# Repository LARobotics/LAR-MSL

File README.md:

# LAR@MSL

## Links
 - [Website] <https://lar.dei.uminho.pt/>
 - [Youtube] <https://www.youtube.com/@lar_uminho>
 - [Instagram] <https://www.instagram.com/lar_uminho>
 - [TikTok] <https://www.tiktok.com/@lar_uminho>
 - [Facebook] <https://www.facebook.com/profile.php?id=100088692420376>

## Our robot: 

# Base Station and Strategy:
The Base Station and Strategy was developed in Python 3.11 and is one of the most important tools for the robots to be able to play. It handles the communications between the Base Station and the robots and even from the RefBox using WebSockets. The Strategy works with the inputs from the robots, calculates the group of skills for that game state, and gives that information back to the robots.

# Calibration Tools:
This folder contains Calibration tools to simplify the calibration of cameras and their alignment. It was made in Python and saves a lot of time when the robot is disassembled and needs to be calibrated.

# Hardware and 3D CADS
Here are available the 3D CAD files from the robot, which is made by either aluminium or plastic PLA. There are still hardware being developed and some of them are from previous team generations, but the ones made this year are available here.

# Player
This is the main robot code that runs on the robot's main computer. It also has the ESP32 code that runs on the Robot Microcontroller.

# Tutorial
Here are some tutorials for the things that are used by the team, for example the use of YOLO, Cameras through Ethernet, Ubuntu installation etc…

# Yolo
In this folder are available Datasets and Code that are used by the Team. It is also being made a version of running the Yolo network in Golang, the language used in the Robot.

### Contacts
 - <fernando@dei.uminho.pt>
 - <gil@dei.uminho.pt>

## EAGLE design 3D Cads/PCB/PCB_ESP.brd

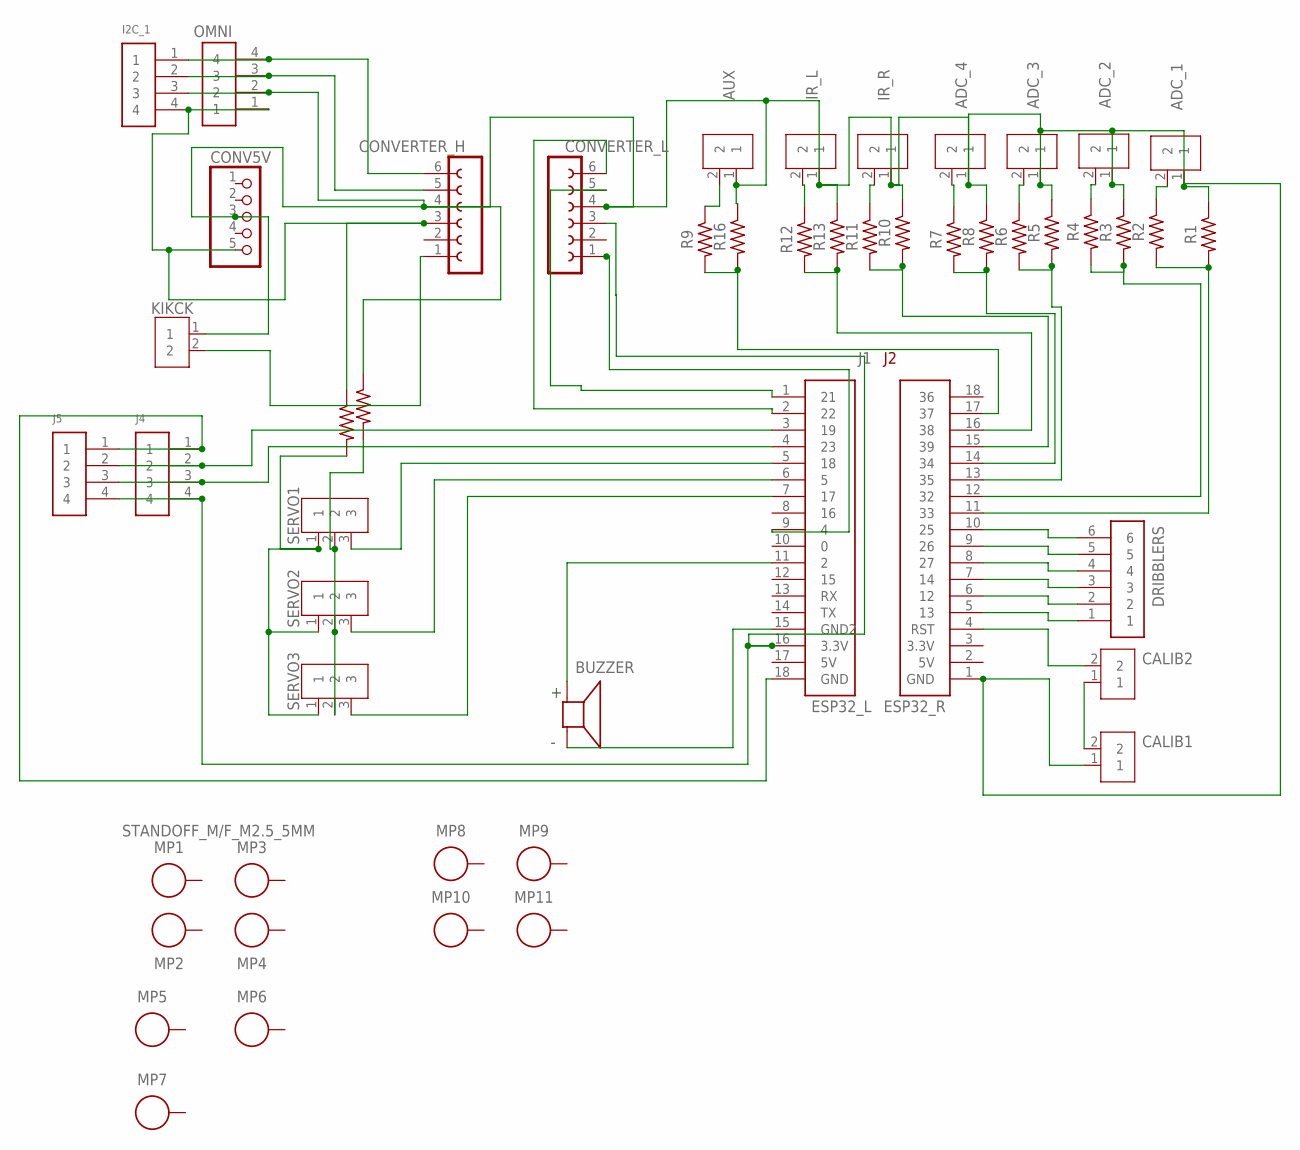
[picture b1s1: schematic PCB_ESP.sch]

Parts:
ADC_1, ADC_2, ADC_3, ADC_4: 2828XX-2282834-2; TERMBLK_254-2N
AUX: 2828XX-2282834-2; TERMBLK_254-2N
BUZZER: AT-1220-TT-9-R; XDCR_AT-1220-TT-9-R
CALIB1, CALIB2: 2828XX-2282834-2; TERMBLK_254-2N
CONV5V: PINHD-1X55X2MM; 1_05X2MM
CONVERTER_H: FE06-1; FE06
CONVERTER_L: FE06-1; FE06
DRIBBLERS: 61300611121
I2C_1: 61300411121
IR_L: 2828XX-2282834-2; TERMBLK_254-2N
IR_R: 2828XX-2282834-2; TERMBLK_254-2N
J1: ESP32_L; 61301811121
J2: ESP32_R; 61301811121
J4, J5: 61300411121
KIKCK: 2828XX-2282834-2; TERMBLK_254-2N
MP1, MP2, MP3, MP4, MP5, MP6, MP7: STANDOFF_M/F_M2.5_5MM; STANDOFF_HEX_MALE-FEMALE_500X500_M2.5X0.45_MTGP755H270
MP8, MP9, MP10, MP11: STANDOFF_F/F_M2.5_5MM; STANDOFF_HEX_FEMALE_500X500_M2.5X0.45_MTGP755H270
OMNI: 61300411121
R1, R2, R3, R4, R5, R6, R7, R8, R9, R10, R11, R12, R13, R14, R15, R16: R-US_AXIAL-7.2MM-PITCH; RESAD724W46L381D178B
SERVO1, SERVO2, SERVO3: 2828XX-3282834-3; TERMBLK_254-3N

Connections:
unnamed: DRIBBLERS.1, J2.5 (13)
unnamed: J2.12 (32), R3.2, R4.2
unnamed: ADC_2.2, R4.1
unnamed: CONVERTER_H.1, KIKCK.2
unnamed: CONVERTER_H.6, I2C_1.1, OMNI.4
unnamed: J2.14 (34), R7.2, R8.2
unnamed: CONVERTER_H.5, I2C_1.2, OMNI.3
unnamed: AUX.2, R9.1
unnamed: J2.13 (35), R5.2, R6.2
unnamed: CONVERTER_L.5, J1.1 (21)
unnamed: CONVERTER_L.6, J1.2 (22)
unnamed: ADC_4.2, R7.1
unnamed: BUZZER.N, J1.15 (GND2)
unnamed: ADC_3.2, R6.1
unnamed: CONV5V.5, CONVERTER_H.3, I2C_1.4, OMNI.1, R14.1
unnamed: BUZZER.P, J1.11 (2)
unnamed: ADC_1.1, ADC_2.1, ADC_3.1, ADC_4.1, AUX.1, CALIB1.1, CONV5V.3, CONVERTER_H.4, CONVERTER_L.4, I2C_1.3, IR_L.1, IR_R.1, J2.1 (GND), KIKCK.1, OMNI.2, R1.1, R3.1, R5.1, R8.1, R10.1, R13.1, R15.1, R16.1
unnamed: CALIB2.2, J2.4 (RST)
unnamed: DRIBBLERS.2, J2.6 (12)
unnamed: DRIBBLERS.3, J2.7 (14)
unnamed: DRIBBLERS.4, J2.8 (27)
unnamed: DRIBBLERS.5, J2.9 (26)
unnamed: DRIBBLERS.6, J2.10 (25)
unnamed: CALIB1.2, CALIB2.1
unnamed: ADC_1.2, R2.1
unnamed: CONVERTER_L.1, J1.9 (4)
unnamed: J2.11 (33), R1.2, R2.2
unnamed: J2.15 (39), R10.2, R11.2
unnamed: IR_L.2, R12.1
unnamed: IR_R.2, R11.1
unnamed: J1.18 (GND), J4.1, J5.1
unnamed: J2.17 (37), R9.2, R16.2
unnamed: J2.16 (38), R12.2, R13.2
unnamed: R14.2, SERVO1.1, SERVO2.1, SERVO3.1
unnamed: R15.2, SERVO1.2, SERVO2.2, SERVO3.2
unnamed: J1.5 (18), SERVO1.3
unnamed: J1.6 (5), SERVO2.3
unnamed: J1.7 (17), SERVO3.3
unnamed: J1.3 (19), J4.2, J5.2
unnamed: J1.4 (23), J4.3, J5.3
unnamed: CONVERTER_L.3, J1.16 (3.3V), J4.4, J5.4

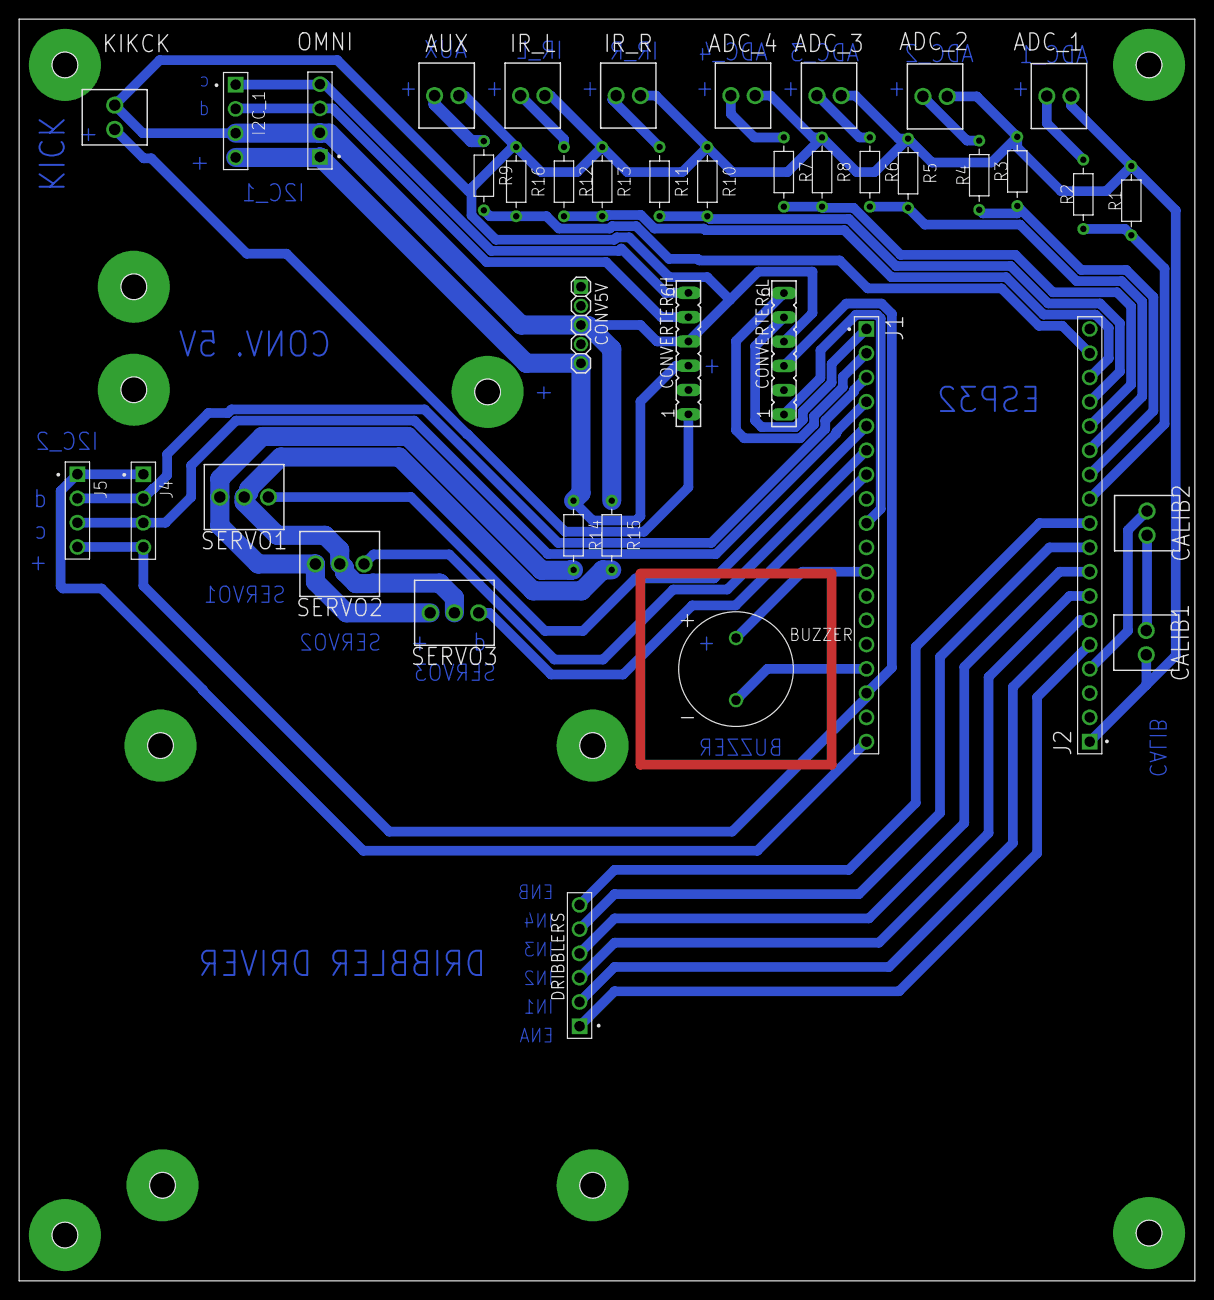
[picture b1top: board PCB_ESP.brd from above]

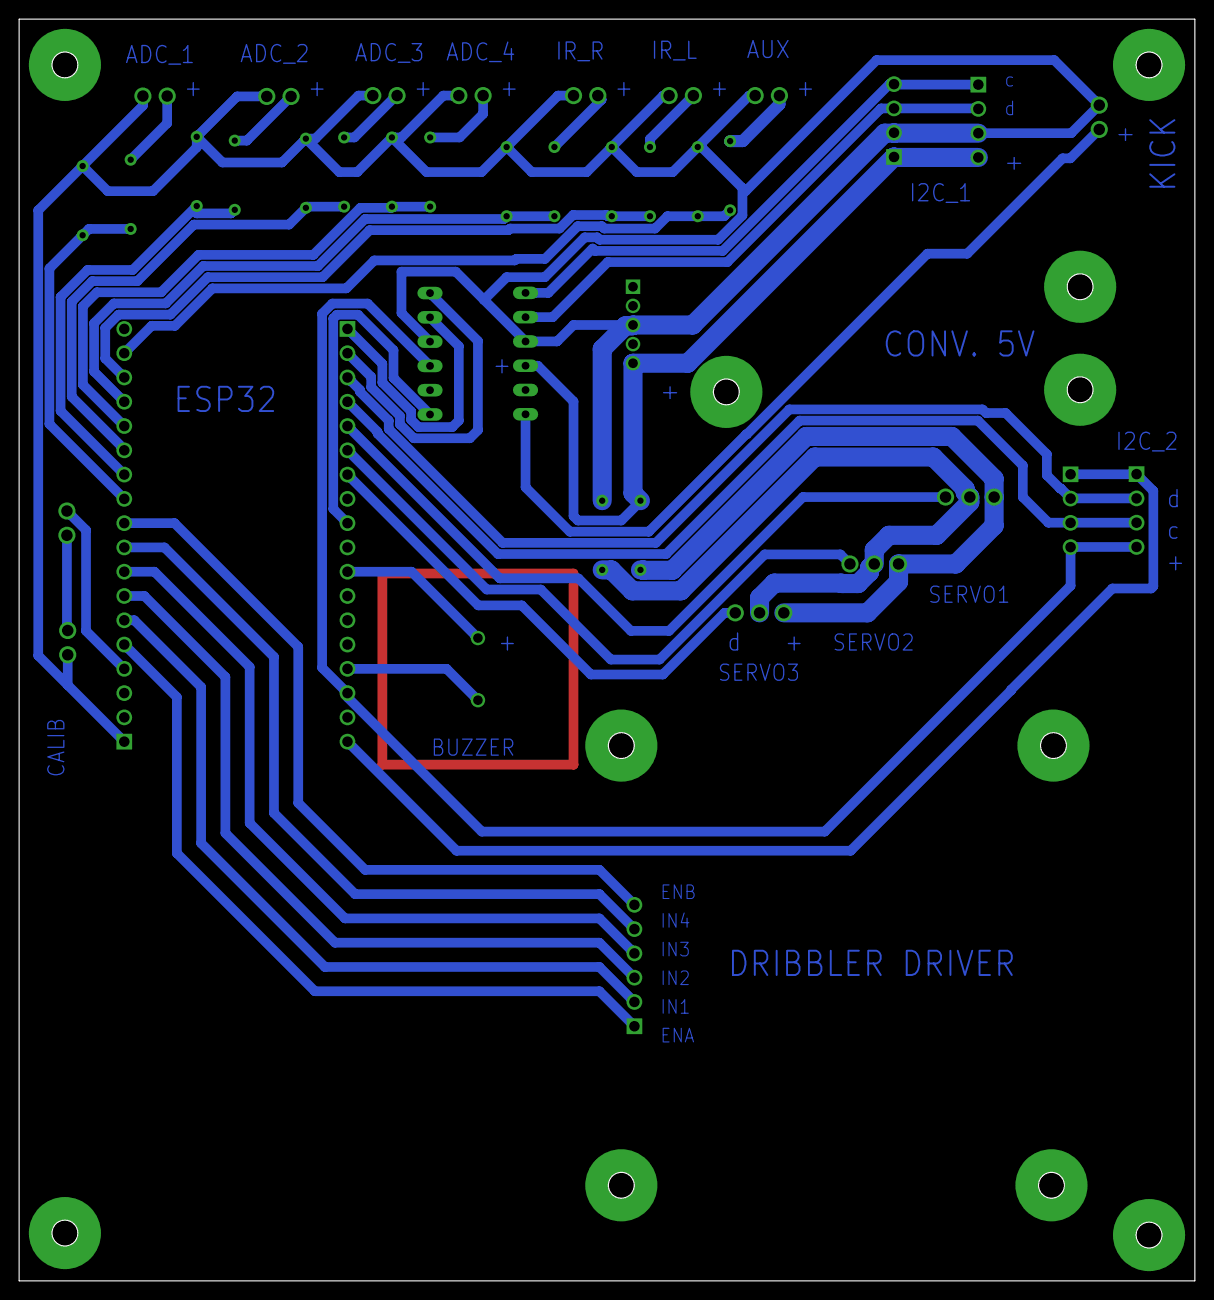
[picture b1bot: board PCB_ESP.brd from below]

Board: 2 copper layers, 123.0 x 132.0 mm, 51 parts (4 on the bottom side), 41 nets.

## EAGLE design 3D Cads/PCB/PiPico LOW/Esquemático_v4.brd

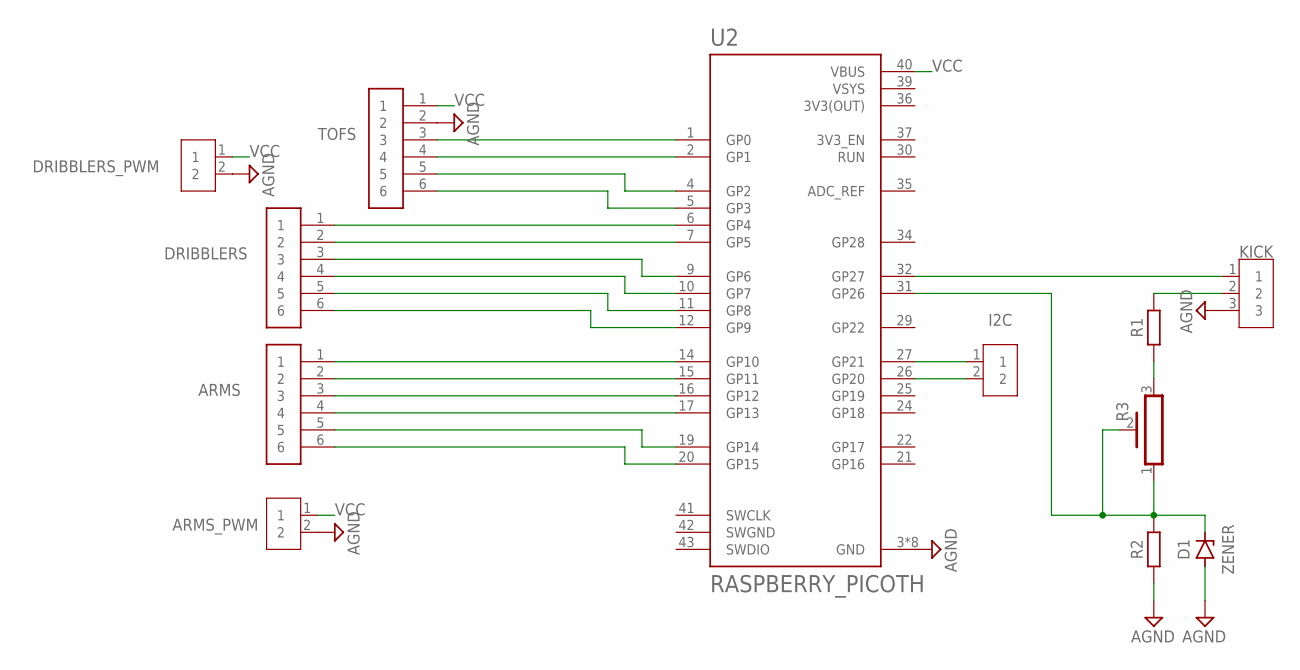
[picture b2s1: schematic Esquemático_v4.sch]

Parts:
ARMS: 691311400106; TERMINALBLOCK_PLUGGABLE-6-7.62MM
ARMS_PWM: 2828XX-2282834-2; TERMBLK_254-2N
D1: ZENER; DIOM7959X625N
DRIBBLERS: 691311400106; TERMINALBLOCK_PLUGGABLE-6-7.62MM
DRIBBLERS_PWM: 2828XX-2282834-2; TERMBLK_254-2N
I2C: 2828XX-2282834-2; TERMBLK_254-2N
KICK: 2828XX-3282837-3; TERMBLK_508-3N
R1, R2: R_AXIAL-7.2MM-PITCH; RESAD724W46L381D178B
R3: PV36Z
TOFS: 691311400106; TERMINALBLOCK_PLUGGABLE-6-7.62MM
U2: RASPBERRY_PICOTH; PICO-PKG-TH

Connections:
3V3(OUT): U2.36 (3V3(OUT))
AGND: ARMS_PWM.2, D1.2 (A), DRIBBLERS_PWM.2, KICK.3, R2.1, TOFS.2, U2.3 (GND), U2.8 (GND), U2.13 (GND), U2.18 (GND), U2.23 (GND), U2.28 (GND), U2.33 (GND), U2.38 (GND)
KICK: TOFS.4, U2.2 (GP1)
unnamed: DRIBBLERS.1, U2.6 (GP4)
unnamed: TOFS.6, U2.5 (GP3)
unnamed: TOFS.5, U2.4 (GP2)
unnamed: DRIBBLERS.2, U2.7 (GP5)
unnamed: DRIBBLERS.3, U2.9 (GP6)
unnamed: DRIBBLERS.4, U2.10 (GP7)
unnamed: DRIBBLERS.5, U2.11 (GP8)
unnamed: DRIBBLERS.6, U2.12 (GP9)
unnamed: ARMS.1, U2.14 (GP10)
unnamed: ARMS.2, U2.15 (GP11)
unnamed: ARMS.3, U2.16 (GP12)
unnamed: ARMS.4, U2.17 (GP13)
unnamed: ARMS.5, U2.19 (GP14)
unnamed: ARMS.6, U2.20 (GP15)
unnamed: KICK.1, U2.32 (GP27)
unnamed: KICK.2, R1.2
unnamed: D1.1 (C), R2.2, R3.1, R3.2, U2.31 (GP26)
unnamed: I2C.1, U2.27 (GP21)
unnamed: I2C.2, U2.26 (GP20)
unnamed: R1.1, R3.3
SWGND: U2.42 (SWGND)
TOF_SDA: TOFS.3, U2.1 (GP0)
VCC: ARMS_PWM.1, DRIBBLERS_PWM.1, TOFS.1
VSYS: U2.39 (VSYS)

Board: 2 copper layers, 12 parts (1 on the bottom side), 24 nets, no tracks yet.

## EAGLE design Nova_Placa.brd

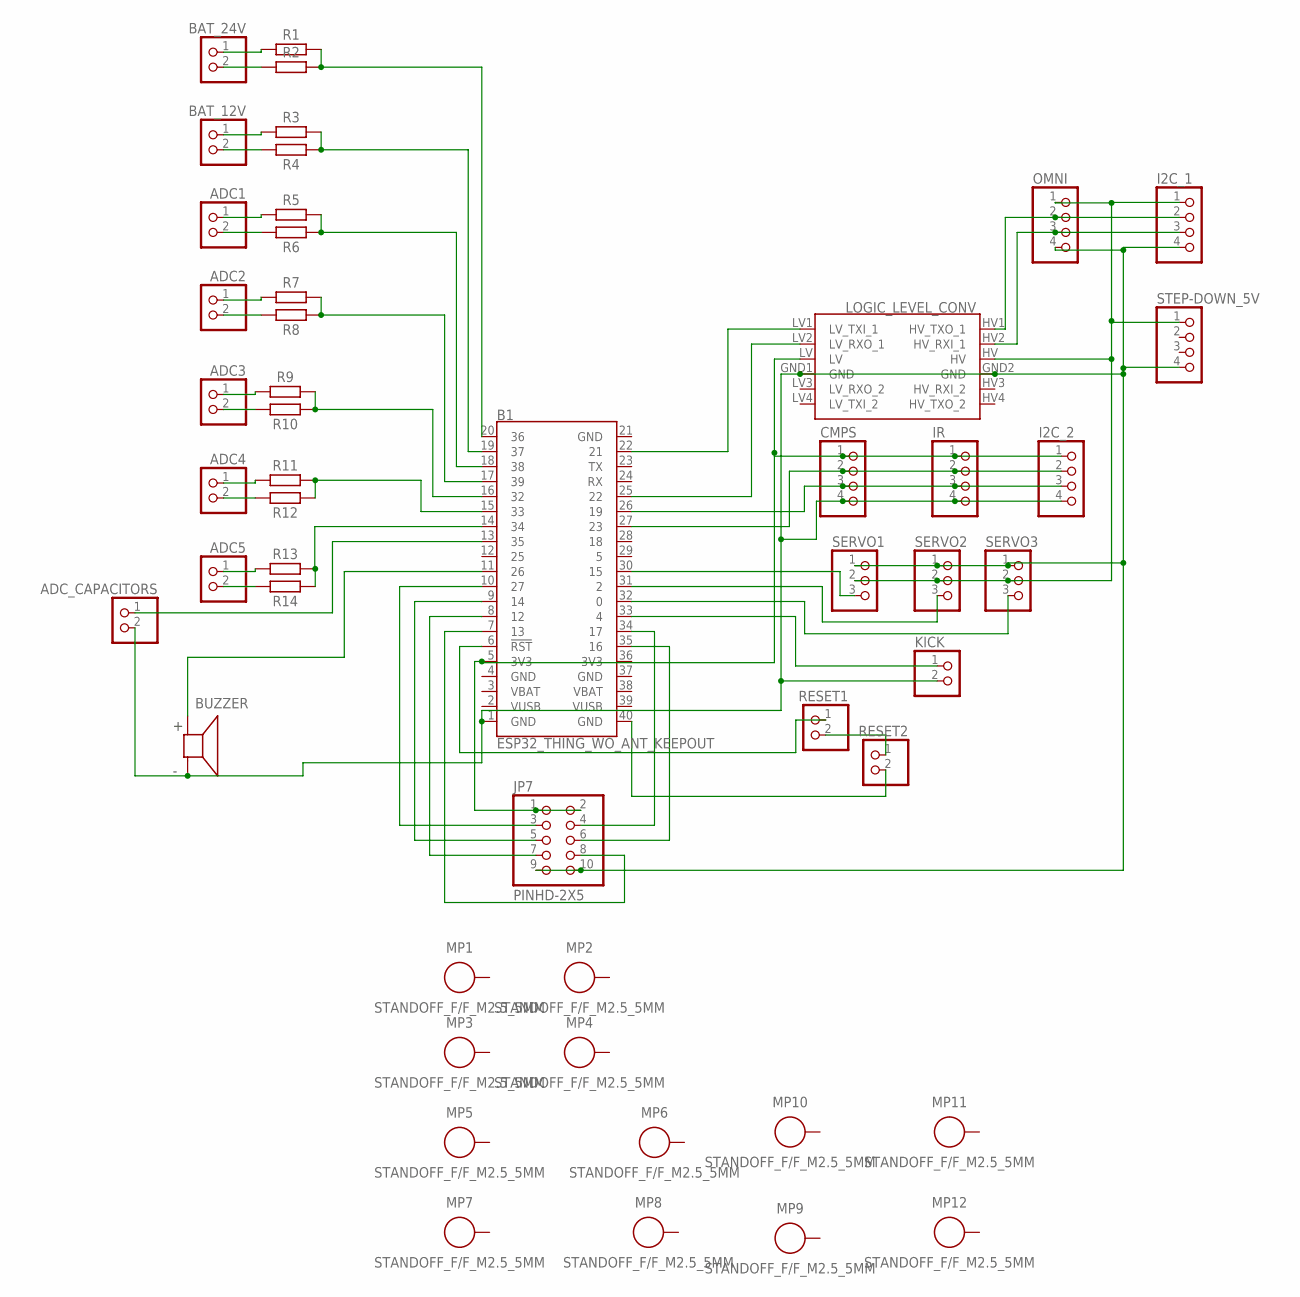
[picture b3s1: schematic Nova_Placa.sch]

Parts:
ADC1, ADC2, ADC3, ADC4, ADC5: PINHD-1X2; 1X02
ADC_CAPACITORS: PINHD-1X2; 1X02
B1: ESP32_THING_WO_ANT_KEEPOUT; ESP32_THING_NO_ANT
BAT_12V, BAT_24V: PINHD-1X2; 1X02
BUZZER: AT-1220-TT-9-R; XDCR_AT-1220-TT-9-R
CMPS: PINHD-1X4; 1X04
I2C_1, I2C_2: PINHD-1X4; 1X04
IR: PINHD-1X4; 1X04
JP7: PINHD-2X5; 2X05
KICK: PINHD-1X2; 1X02
LOGIC_LEVEL_CONV: SPARKFUN_LOGIC_LEVEL_CONVERTERLOCK; SPARKFUN_LOGIC_LEVEL_CONVERTER_LOCK
MP1, MP2, MP3, MP4, MP5, MP6, MP7, MP8, MP9, MP10, MP11, MP12: STANDOFF_F/F_M2.5_5MM; STANDOFF_HEX_FEMALE_500X500_M2.5X0.45_MTGP755H270
OMNI: PINHD-1X4; 1X04
R1, R2, R3, R4, R5, R6, R7, R8, R9, R10, R11, R12, R13, R14: R_AXIAL-7.2MM-PITCH; RESAD724W46L381D178B
RESET1, RESET2: PINHD-1X2; 1X02
SERVO1, SERVO2, SERVO3: PINHD-1X3; 1X03
STEP-DOWN_5V: PINHD-1X4; 1X04

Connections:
unnamed: B1.35 (16), JP7.6
unnamed: ADC_CAPACITORS.2, B1.1 (GND), BUZZER.N, CMPS.4, I2C_1.4, I2C_2.4, IR.4, JP7.9, JP7.10, KICK.2, LOGIC_LEVEL_CONV.GND1 (GND), LOGIC_LEVEL_CONV.GND2 (GND), OMNI.4, SERVO1.1, SERVO2.1, SERVO3.1, STEP-DOWN_5V.4
unnamed: B1.22 (21), LOGIC_LEVEL_CONV.LV1 (LV_TXI_1)
unnamed: B1.25 (22), LOGIC_LEVEL_CONV.LV2 (LV_RXO_1)
unnamed: B1.5 (3V3), CMPS.1, I2C_2.1, IR.1, JP7.1, JP7.2, LOGIC_LEVEL_CONV.LV
unnamed: I2C_1.1, LOGIC_LEVEL_CONV.HV, OMNI.1, SERVO1.2, SERVO2.2, SERVO3.2, STEP-DOWN_5V.1
unnamed: B1.27 (23), CMPS.2, I2C_2.2, IR.2
unnamed: B1.26 (19), CMPS.3, I2C_2.3, IR.3
unnamed: I2C_1.2, LOGIC_LEVEL_CONV.HV1 (HV_TXO_1), OMNI.2
unnamed: I2C_1.3, LOGIC_LEVEL_CONV.HV2 (HV_RXI_1), OMNI.3
unnamed: RESET1.2, RESET2.1
unnamed: B1.34 (17), JP7.4
unnamed: B1.7 (13), JP7.8
unnamed: B1.8 (12), JP7.7
unnamed: B1.9 (14), JP7.5
unnamed: B1.10 (27), JP7.3
unnamed: ADC5.1, R13.1
unnamed: ADC5.2, R14.1
unnamed: B1.14 (34), R13.2, R14.2
unnamed: ADC4.2, R12.1
unnamed: B1.15 (33), R11.2, R12.2
unnamed: ADC4.1, R11.1
unnamed: ADC3.2, R10.1
unnamed: ADC3.1, R9.1
unnamed: B1.16 (32), R9.2, R10.2
unnamed: ADC2.2, R8.1
unnamed: ADC2.1, R7.1
unnamed: B1.33 (4), KICK.1
unnamed: ADC1.2, R6.1
unnamed: ADC1.1, R5.1
unnamed: B1.18 (38), R5.2, R6.2
unnamed: BAT_12V.2, R4.1
unnamed: BAT_12V.1, R3.1
unnamed: B1.19 (37), R3.2, R4.2
unnamed: BAT_24V.2, R2.1
unnamed: BAT_24V.1, R1.1
unnamed: B1.20 (36), R1.2, R2.2
unnamed: B1.17 (39), R7.2, R8.2
unnamed: B1.32 (0), SERVO3.3
unnamed: B1.31 (2), SERVO2.3
unnamed: B1.30 (15), SERVO1.3
unnamed: B1.40 (GND), RESET2.2
unnamed: B1.11 (26), BUZZER.P
unnamed: ADC_CAPACITORS.1, B1.13 (35)
unnamed: B1.6 (!RST!), RESET1.1

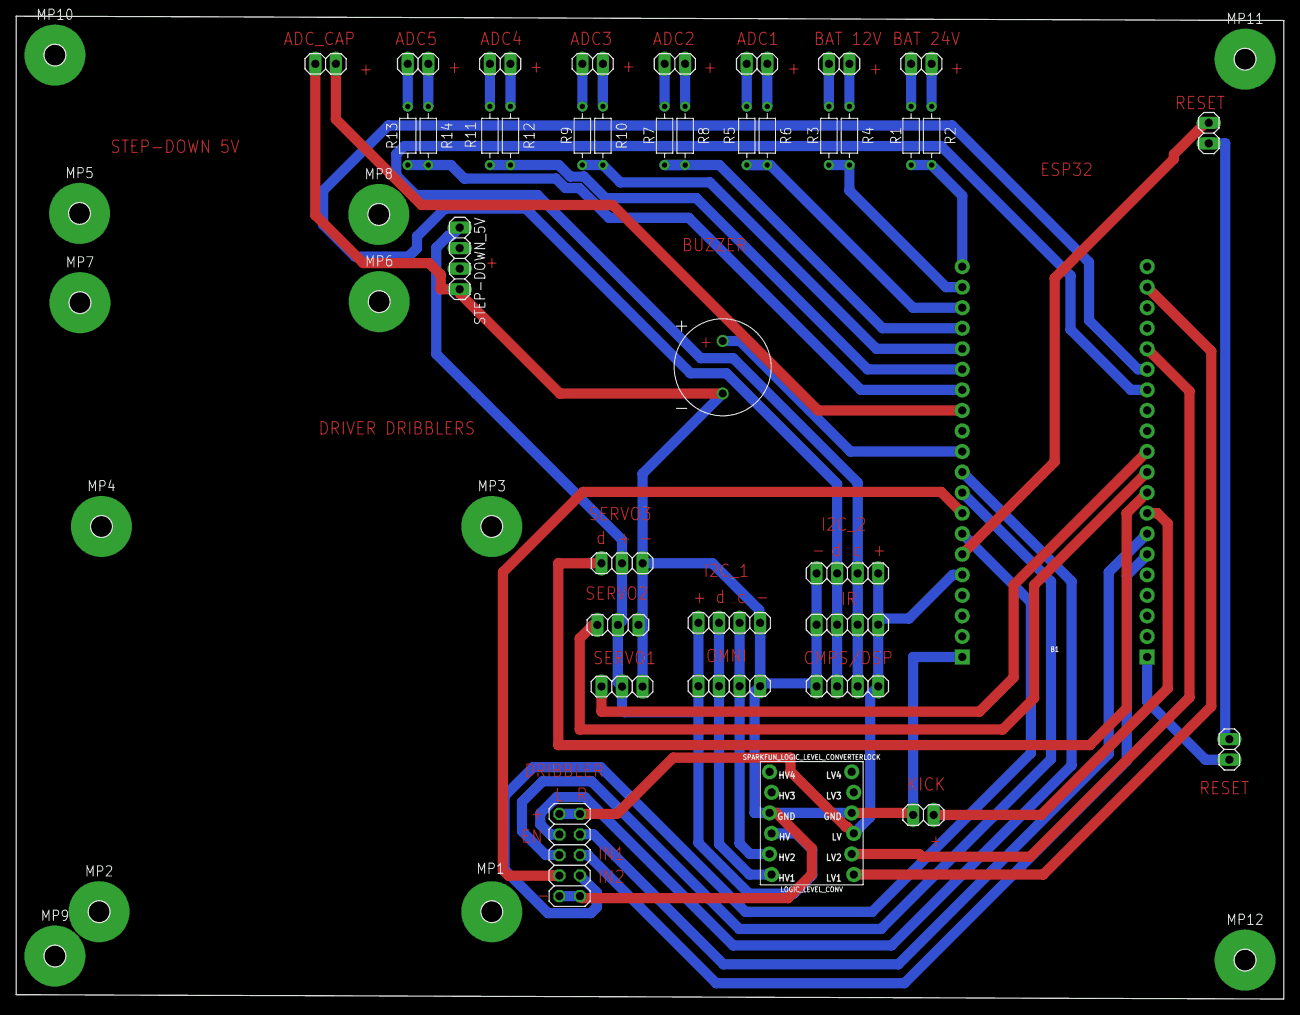
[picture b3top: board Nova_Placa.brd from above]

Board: 2 copper layers, 156.7 x 121.5 mm, 50 parts (0 on the bottom side), 45 nets.

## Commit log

2023-03-16 Add all CAD Files
2023-03-21 Add MES
2024-02-29 TDP 2024
2025-02-26 Create 2023
2025-02-26 Create 2023
    New Folder
2025-02-26 Create mmm
2025-02-26 Create awaa
2025-02-26 Create awda
2025-02-26 Create adaw
2025-02-26 Create awdawda
2025-02-26 Create awdawdawdawd
2025-02-26 Create awdadawd
2025-02-26 Create awdadawdw
2025-02-26 Create offf
2025-02-26 Create ooof
2025-02-26 Create off
2025-02-26 Create awdawdawd
2025-02-26 Create oooof
2025-02-26 Create oooooooof
2025-02-26 Create scscsdc
2025-02-26 Create awdadawdawd
2025-02-26 Create adawdawdawd
2025-02-26 Create oof
2025-02-26 Create wadawdawd
2025-02-26 Create oooooof
2025-02-26 Create ooooooof
2025-02-26 Create adwadawd
2025-02-26 Create adawdwad
2025-02-26 Create MSL_2025
2025-02-26 TDP 2025
2025-02-26 TSP 2025
2026-02-26 TDP 2026

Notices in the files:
parts and their libraries:
SparkFun-Boards: Licensing: Creative Commons ShareAlike 4.0 International - https://creativecommons.org/licenses/by-sa/4.0
